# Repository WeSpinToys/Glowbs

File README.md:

# Glowbs

This is where you got to upload all you new software iteration as fast as your little fingers can commit

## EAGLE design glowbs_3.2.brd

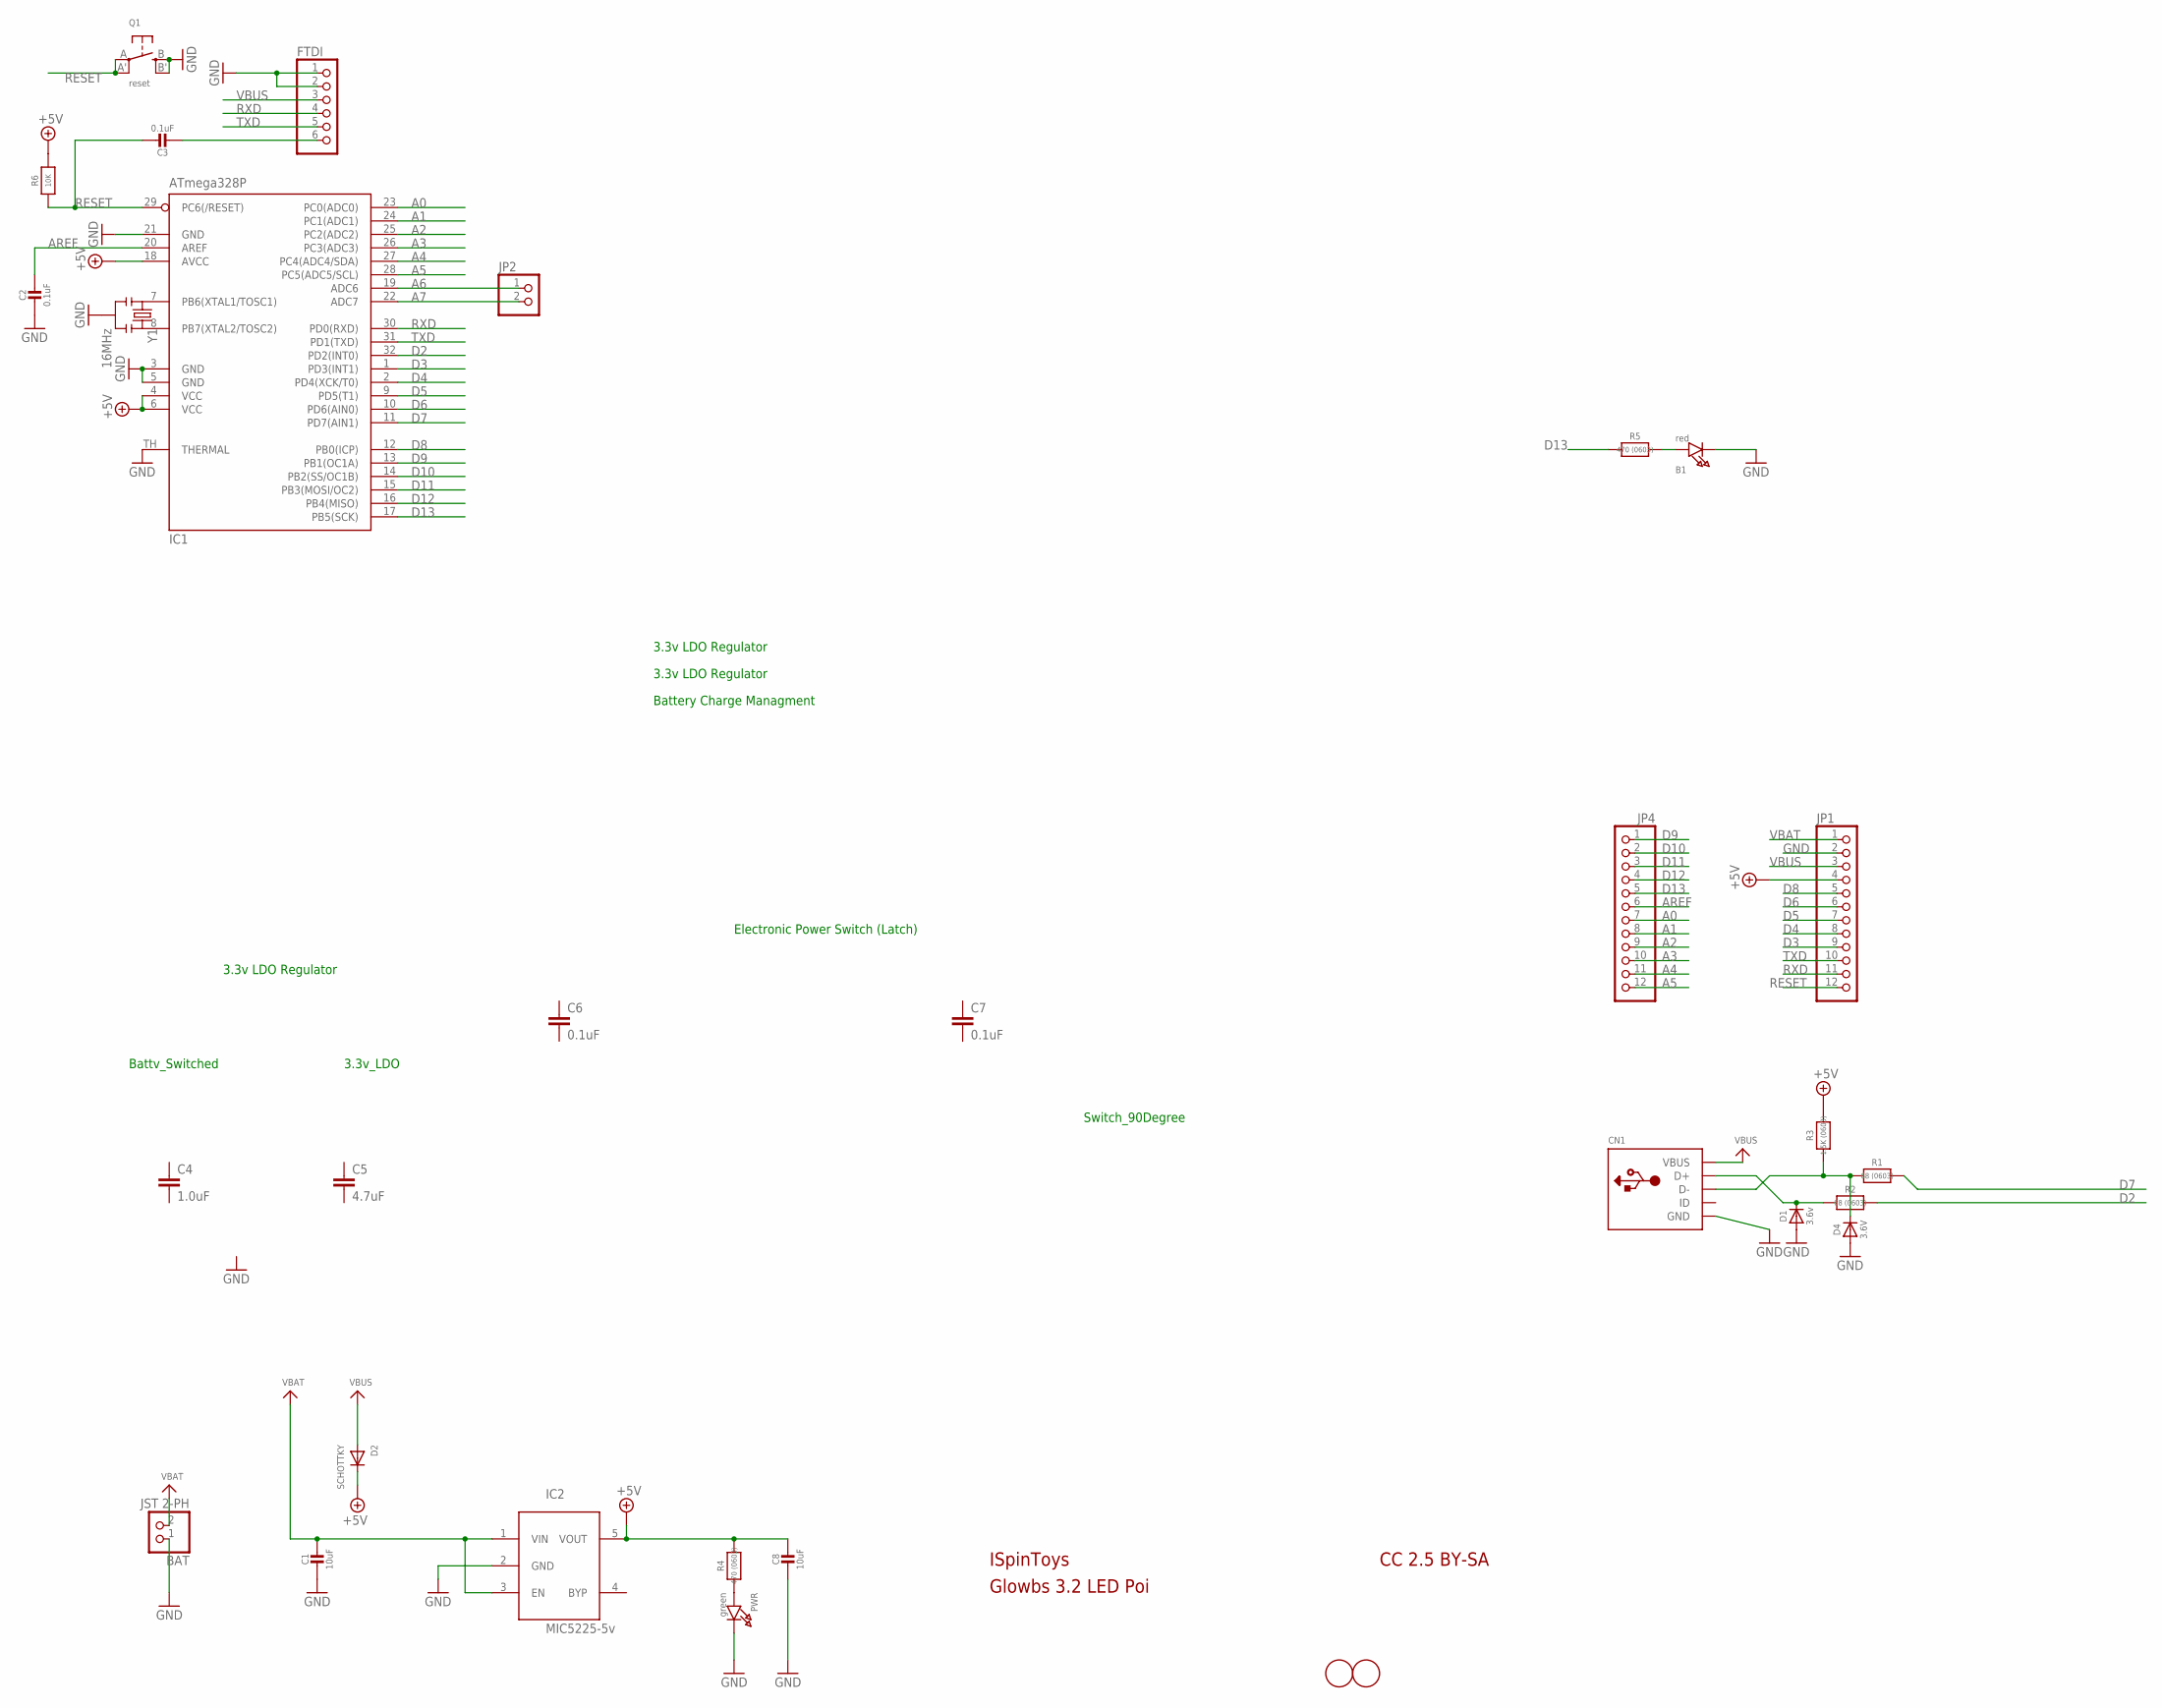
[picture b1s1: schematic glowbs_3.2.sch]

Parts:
B1: red; CHIPLED_0805_NOOUTLINE
BAT: JST 2-PH; JSTPH2
C1, C8: 10uF; 0805-NO
C2: 0.1uF; _0805MP
C3: 0.1uF; 0805-NO
C4: 1.0uF; 0603-CAP
C5: 4.7uF; 0603-CAP
C6, C7: 0.1uF; 0603-CAP
CN1: USBMICRO_20329; 4UCONN_20329
D1: 3.6v; SOD-323
D2: SCHOTTKY; SOD-123FL
D4: 3.6V; SOD-323
FTDI: PINHD-1X6CB; 1X06-CLEANBIG
IC1: ATmega328P; MLF32-TH
IC2: MIC5225-5v; SOT23-5L
JP1, JP4: PINHD-1X12-CB; 1X12-CB
JP2: HEADER-1X2ROUND; 1X02_ROUND
PWR: green; CHIPLED_0805_NOOUTLINE
Q1: reset; BTN_KMR2_4.6X2.8
R1, R2: 68 (0603); 0603-NO
R3: 1.5K (0603); 0603-NO
R4, R5: 470 (0603); 0603-NO
R6: 10K; 0805-NO
U$1, U$6: FIDUCIAL; FIDUCIAL_1MM
Y1: 16MHz; RESONATOR-SMD

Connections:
+5V: C8.1, D2.C, IC1.4 (VCC), IC1.6 (VCC), IC1.18 (AVCC), IC2.5 (VOUT), JP1.4, R3.2, R4.2, R6.2
A0: IC1.23 (PC0(ADC0)), JP4.7
A1: IC1.24 (PC1(ADC1)), JP4.8
A2: IC1.25 (PC2(ADC2)), JP4.9
A3: IC1.26 (PC3(ADC3)), JP4.10
A4: IC1.27 (PC4(ADC4/SDA)), JP4.11
A5: IC1.28 (PC5(ADC5/SCL)), JP4.12
A6: IC1.19 (ADC6), JP2.1
A7: IC1.22 (ADC7), JP2.2
AREF: C2.1, IC1.20 (AREF), JP4.6
D2: IC1.32 (PD2(INT0)), R2.2
D3: IC1.1 (PD3(INT1)), JP1.9
D4: IC1.2 (PD4(XCK/T0)), JP1.8
D5: IC1.9 (PD5(T1)), JP1.7
D6: IC1.10 (PD6(AIN0)), JP1.6
D7: IC1.11 (PD7(AIN1)), R1.2
D8: IC1.12 (PB0(ICP)), JP1.5
D9: IC1.13 (PB1(OC1A)), JP4.1
D10: IC1.14 (PB2(SS/OC1B)), JP4.2
D11: IC1.15 (PB3(MOSI/OC2)), JP4.3
D12: IC1.16 (PB4(MISO)), JP4.4
D13: IC1.17 (PB5(SCK)), JP4.5, R5.2
D+: CN1.D+, D1.C, R2.1
D-: CN1.D-, D4.C, R1.1, R3.1
DTR/RTS: C3.2, FTDI.6
GND: B1.C, BAT.1, C1.2, C2.2, C8.2, CN1.BASE@1 (GND), CN1.BASE@2 (GND), CN1.GND, CN1.SPRT@1 (GND), CN1.SPRT@2 (GND), CN1.SPRT@3 (GND), CN1.SPRT@4 (GND), D1.A, D4.A, FTDI.1, FTDI.2, IC1.3 (GND), IC1.5 (GND), IC1.21 (GND), IC1.TH (THERMAL), IC2.2 (GND), JP1.2, PWR.C, Q1.B (S), Q1.B' (S1), Y1.2
unnamed: B1.A, R5.1
unnamed: IC1.8 (PB7(XTAL2/TOSC2)), Y1.3
unnamed: IC1.7 (PB6(XTAL1/TOSC1)), Y1.1
unnamed: PWR.A, R4.1
RESET: C3.1, IC1.29 (PC6(/RESET)), JP1.12, Q1.A, Q1.A' (P1), R6.1
RXD: FTDI.4, IC1.30 (PD0(RXD)), JP1.11
TXD: FTDI.5, IC1.31 (PD1(TXD)), JP1.10
VBAT: BAT.2, C1.1, IC2.1 (VIN), IC2.3 (EN), JP1.1
VBUS: CN1.VBUS, D2.A, FTDI.3, JP1.3

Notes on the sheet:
ISpinToys
Glowbs 3.2 LED Poi
CC 2.5 BY-SA
3.3v LDO Regulator
Battery Charge Managment
Electronic Power Switch (Latch)
Battv_Switched
3.3v_LDO
Switch_90Degree

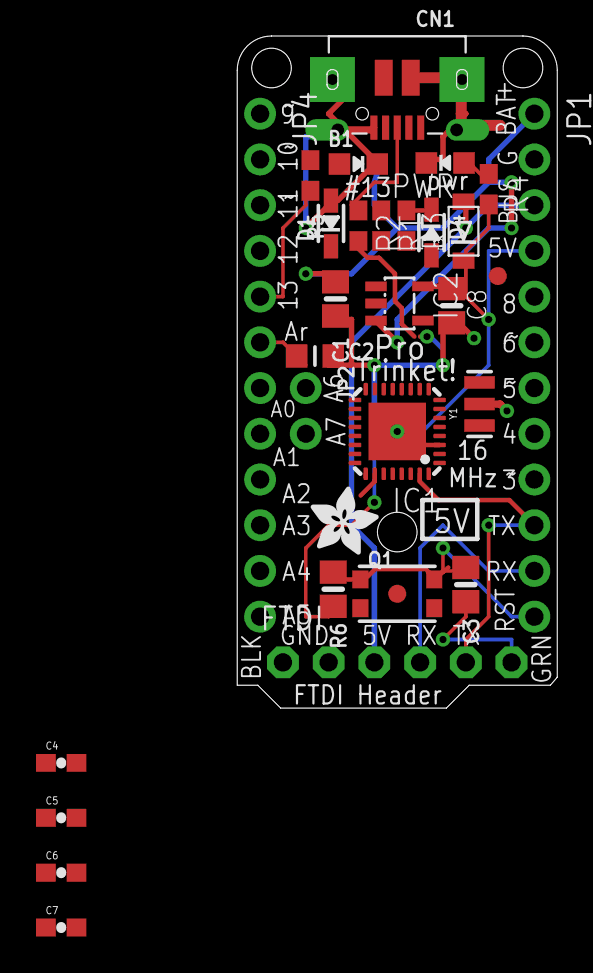
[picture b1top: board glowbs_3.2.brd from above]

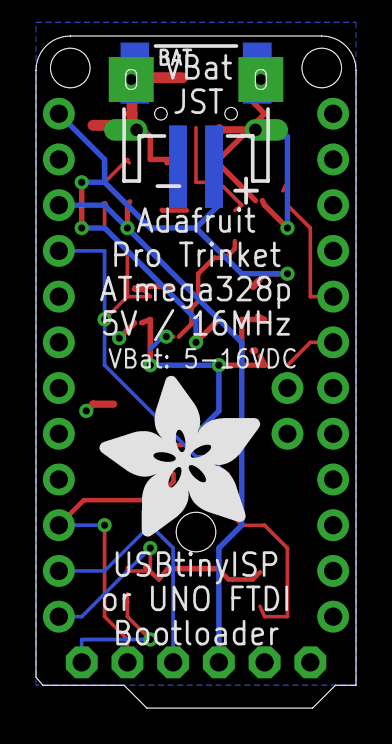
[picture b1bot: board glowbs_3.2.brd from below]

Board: 2 copper layers, 17.8 x 37.3 mm, 33 parts (2 on the bottom side), 35 nets.

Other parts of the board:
U$7: ADAFRUIT_3.5MM
U$9: ADAFRUIT_9MM

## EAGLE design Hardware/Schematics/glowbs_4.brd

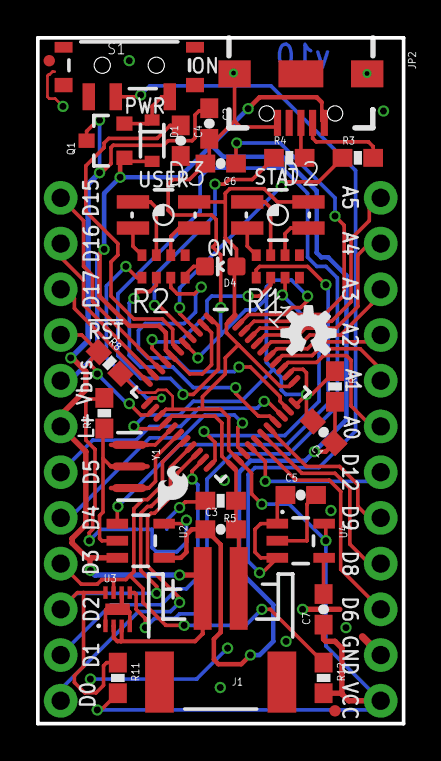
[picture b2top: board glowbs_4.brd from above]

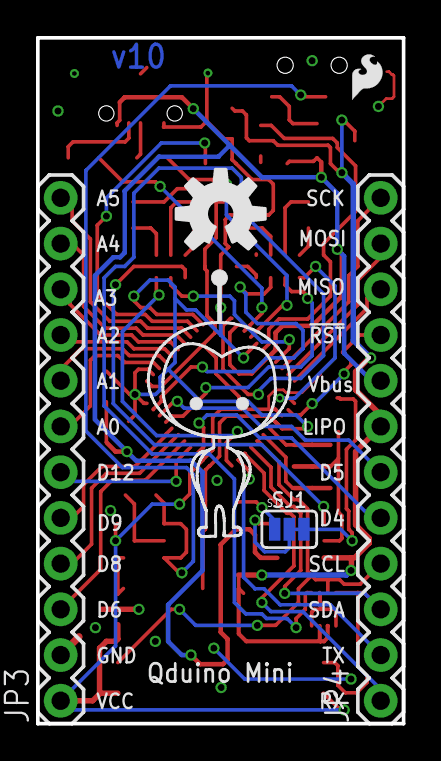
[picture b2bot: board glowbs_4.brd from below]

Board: 2 copper layers, 20.3 x 38.1 mm, 41 parts (6 on the bottom side), 51 nets.

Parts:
C1, C2: 4.7uF; 0603-CAP
C3, C4, C5: 1uF; 0603-CAP
C6: 0.1uF; 0603-CAP
C7: 2.2uF; 0603-CAP
D1: BAT20J; SOD-323
D2, D3: P-LCC-4-3
D4: POWER; LED-0603
FID1, FID2: FIDUCIALUFIDUCIAL; MICRO-FIDUCIAL
FRAME2: CREATIVE_COMMONS
J1: LiPo; JST-2-SMD
JP2: USB-B-MICRO-SMD_V03
JP3, JP4: 1X12
LOGO1: OSHW-LOGOS; OSHW-LOGO-S
LOGO2: SFE_LOGO_FLAME.1_INCH; SFE_LOGO_FLAME_.1
LOGO3: SFE_LOGO_FLAME.1_INCH; SFE_LOGO_FLAME_.1@1
Q1: ZXMP6A13FTA; SOT23-3
R1, R2: 1KΩ; 0603-ARV
R3, R4: 22; 0603-RES
R5: 2.0k; 0603-RES
R6: 100k; 0603-RES
R7, R8: 10K; 0603-RES
R11, R12: 4.7K; 0603-RES
S1: POWER; SWITCH-SPST-SMD-A
SJ1: PAD-JUMPER-3-2OF3_NC_BY_TRACE_YES_SILK_FULL_BOX
U1: ATMEGA32U41:1-LESS_PASTE; QFN-44-NOPAD_1:1-LESS_PASTE
U2: MCP73831; SOT23-5
U3: MAX17048; DFN-8
U4: AP2112K-3.3TRG-1; SOT23-5
U5: MIGHTYQ-L-SILK; LOGO-LARGE-SILK
U$4: OSHW-LOGO-M
Y1: 8MHZ; RESONATOR-SMD

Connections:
!ALRT: U1.1, U3.P$5
!RST: JP4.9, R8.1, U1.13
A0: JP3.7, U1.36
A1: JP3.8, U1.37
A2: JP3.9, U1.38
A3: JP3.10, U1.39
A4: JP3.11, U1.40
A5: JP3.12, U1.41
AREF: C6.1, U1.42
D4: JP4.5, U1.25
D5: JP4.6, U1.31
D6: JP3.3, U1.27
D8: JP3.4, U1.28
D9: JP3.5, U1.29
D10: R2.2, U1.30
D11: R2.1, U1.12
D12: JP3.6, U1.26
D13: R2.3, U1.32
D+: R4.1, U1.4
D-: R3.1, U1.3
GND: C1.2, C2.2, C3.2, C4.2, C5.2, C6.2, C7.2, J1.1, JP2.GND1, JP2.SHIELD1, JP2.SHIELD2, JP2.SHIELD3, JP3.2, R2.5, R5.1, R6.1, R7.1, U1.5, U1.15, U1.23, U1.33, U1.35, U1.43, U2.2, U3.P$1, U3.P$4, U3.P$6, U3.P$9, U4.2, U4.4, Y1.2
INMOSFET: D1.C, Q1.2, S1.3
LIPO: C2.1, J1.2, JP4.7, Q1.3, U2.3, U3.P$2, U3.P$3
MISO: JP4.10, U1.11
MOSI: JP4.11, U1.10
unnamed: D2.3, R1.6
unnamed: D2.2, R1.8
unnamed: D3.3, R2.6
unnamed: D4.C, R2.4
unnamed: R7.2, SJ1.3
unnamed: R5.2, SJ1.1
unnamed: D3.2, R2.8
unnamed: D2.1, R1.7
unnamed: D3.1, R2.7
PROG: SJ1.2, U2.5
RX: JP4.1, U1.20
RXLED: R1.2, U1.8
SCK: JP4.12, U1.9
SCL: JP4.4, R12.1, U1.18, U3.P$7
SDA: JP4.3, R11.1, U1.19, U3.P$8
STAT: R1.1, U2.1
TX: JP4.2, U1.21
TXLED: R1.3, U1.22
UCAP: C4.1, U1.6
UD+: JP2.D+1, R4.2
UD-: JP2.D-1, R3.2
VBUS: C1.1, C3.1, D1.A, JP2.VBUS1, JP4.8, Q1.1, R6.2, U1.2, U1.7, U2.4
VCC: C7.1, D2.4, D3.4, D4.A, JP3.1, R8.2, R11.2, R12.2, U1.14, U1.24, U1.34, U1.44, U4.5
VINPUT: C5.1, S1.2, U4.1, U4.3
X1: U1.17, Y1.3
X2: U1.16, Y1.1

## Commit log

2016-09-23 Added btserver.ino
2016-09-23 This is the first commit of the hardware and software development teamm!
    The change is necessary!
    /usr/bin/bash: q: command not found
2016-09-23 Moved btserver.ino to Software folder
2016-09-23 This is the new shit
    Folder Hierarchy Changes
    i
2016-09-23 Hey there everyone
    This is another move
2016-09-23 Moved btserver.ino into Bluetooth
2016-09-23 We are working in parallel but attacking the problem from two directions
    Btserver is listening probe like reciever
2016-09-23 Check out these
    https://www.nordicsemi.com/eng/Products/Bluetooth-low-energy/nRF51822
2016-09-23 This is a new change for everyone
    THIS IS A NEW LINE:w
2016-09-23 Drivers from the github
    Install them! We can communicate via C low-level to the rf - unit in the
    device
2016-09-24 Adding Processing Libraries
    take note:`
2016-09-24 EVEN MORE
    UPDATES:
2016-09-24 IOT SDK IMPLEMENTATION
    This is a neccessary evil
2016-09-24 Another IOTSDK commit
    YO
2016-09-24 Finalizing Changes
    YES
2016-09-24 Thank You FOR THE WAREZ
    everyone is the best
2016-09-24 Late Night changes
    spoopy
2016-09-24 This is great
    Nice
2016-09-24 Adding 3D models to the folder
    These are 3D models! Yay
2016-09-29 Atmel Debugging
2016-10-06 Bluetooth Stack
2016-10-10 GOTIT
2016-10-10 library updates
2016-10-13 Rotational Color Selection Experiment
2016-10-13 another one
2016-10-13 Arduino

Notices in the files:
parts and their libraries:
SparkFun-Passives: Licensing: CC v3.0 Share-Alike You are welcome to use this library for commercial purposes.
SparkFun-Aesthetics: Released under the Creative Commons Attribution Share-Alike 4.0 License
SparkFun-Aesthetics: https://creativecommons.org/licenses/by-sa/4.0
